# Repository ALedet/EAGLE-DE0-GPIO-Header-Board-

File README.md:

# ALTERA_DE0_GPIO_HEADER
Altera DE0 GPIO header connector board made in EAGLE.

DRC file used is from OSHPark

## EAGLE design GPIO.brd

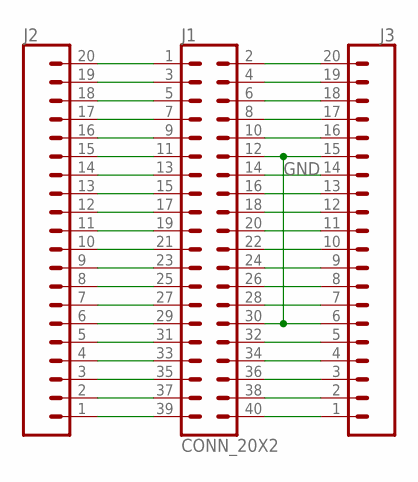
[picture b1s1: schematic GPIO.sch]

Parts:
J1: CONN_20X2; 2X20
J2, J3: CONN_20; 1X20

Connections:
GND: J1.12, J1.30, J3.6, J3.15
unnamed: J1.40, J3.1
unnamed: J1.38, J3.2
unnamed: J1.36, J3.3
unnamed: J1.34, J3.4
unnamed: J1.32, J3.5
unnamed: J1.28, J3.7
unnamed: J1.26, J3.8
unnamed: J1.24, J3.9
unnamed: J1.22, J3.10
unnamed: J1.20, J3.11
unnamed: J1.18, J3.12
unnamed: J1.16, J3.13
unnamed: J1.14, J3.14
unnamed: J1.10, J3.16
unnamed: J1.8, J3.17
unnamed: J1.6, J3.18
unnamed: J1.4, J3.19
unnamed: J1.2, J3.20
unnamed: J1.39, J2.1
unnamed: J1.37, J2.2
unnamed: J1.35, J2.3
unnamed: J1.33, J2.4
unnamed: J1.31, J2.5
unnamed: J1.29, J2.6
unnamed: J1.27, J2.7
unnamed: J1.25, J2.8
unnamed: J1.23, J2.9
unnamed: J1.21, J2.10
unnamed: J1.19, J2.11
unnamed: J1.17, J2.12
unnamed: J1.15, J2.13
unnamed: J1.13, J2.14
unnamed: J1.11, J2.15
unnamed: J1.9, J2.16
unnamed: J1.7, J2.17
unnamed: J1.5, J2.18
unnamed: J1.3, J2.19
unnamed: J1.1, J2.20

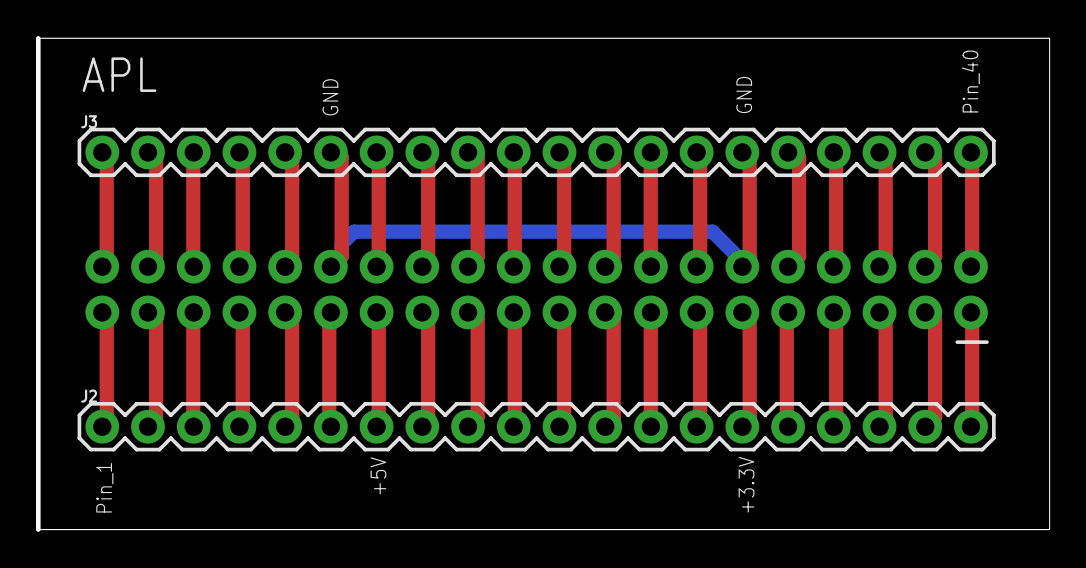
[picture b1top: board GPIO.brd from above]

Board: 2 copper layers, 56.2 x 27.3 mm, 4 parts (1 on the bottom side), 39 nets.

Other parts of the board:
U$1: A3L-LOC

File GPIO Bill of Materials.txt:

Partlist exported from C:/Users/Aryk Ledet/Pictures/eagle/AL_GPIO/GPIO.sch at 4/25/2018 3:37 PM

Part Value     Device    Package Description                                                                                                     
J1   CONN_20X2 CONN_20X2 2X20    Multi connection point. Often used as Generic Header-pin footprint for 0.1 inch spaced/style header connections 
J2   1         CONN_20   1X20    Multi connection point. Often used as Generic Header-pin footprint for 0.1 inch spaced/style header connections 
J3   1         CONN_20   1X20    Multi connection point. Often used as Generic Header-pin footprint for 0.1 inch spaced/style header connections 

Manufacturer	OSHPark		https://oshpark.com/

Male Pins      SparkFun		https://www.sparkfun.com/products/116

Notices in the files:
parts and their libraries:
SparkFun-Connectors: Licensing: Creative Commons ShareAlike 4.0 International - https://creativecommons.org/licenses/by-sa/4.0
